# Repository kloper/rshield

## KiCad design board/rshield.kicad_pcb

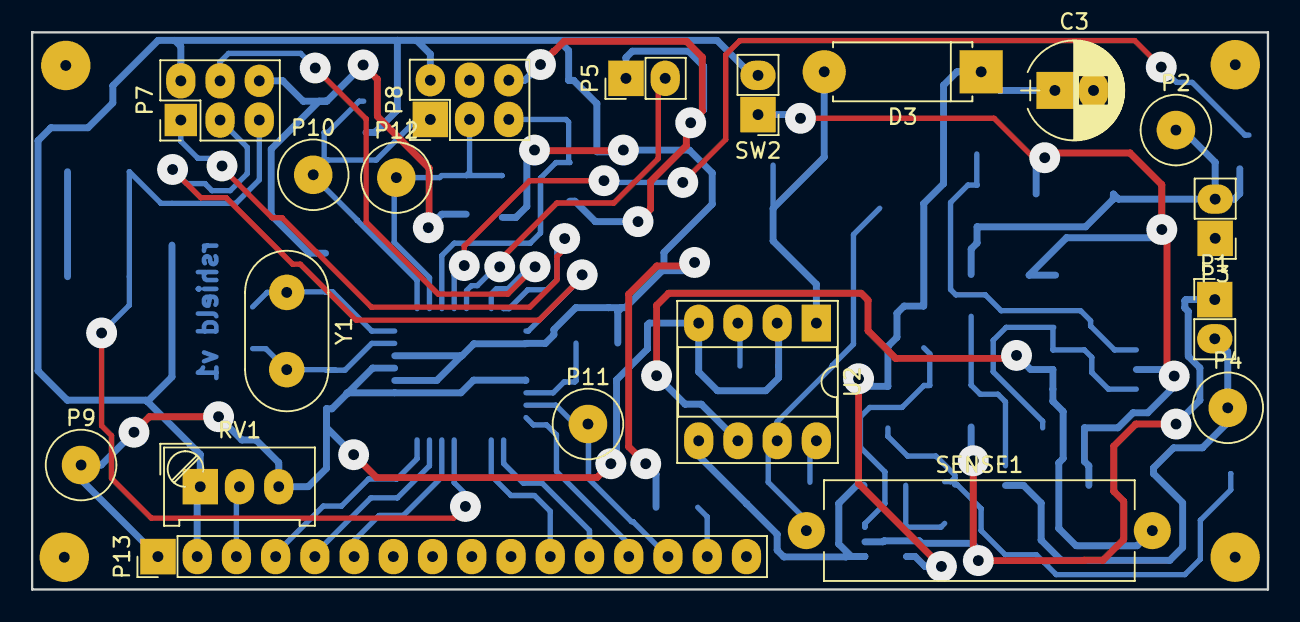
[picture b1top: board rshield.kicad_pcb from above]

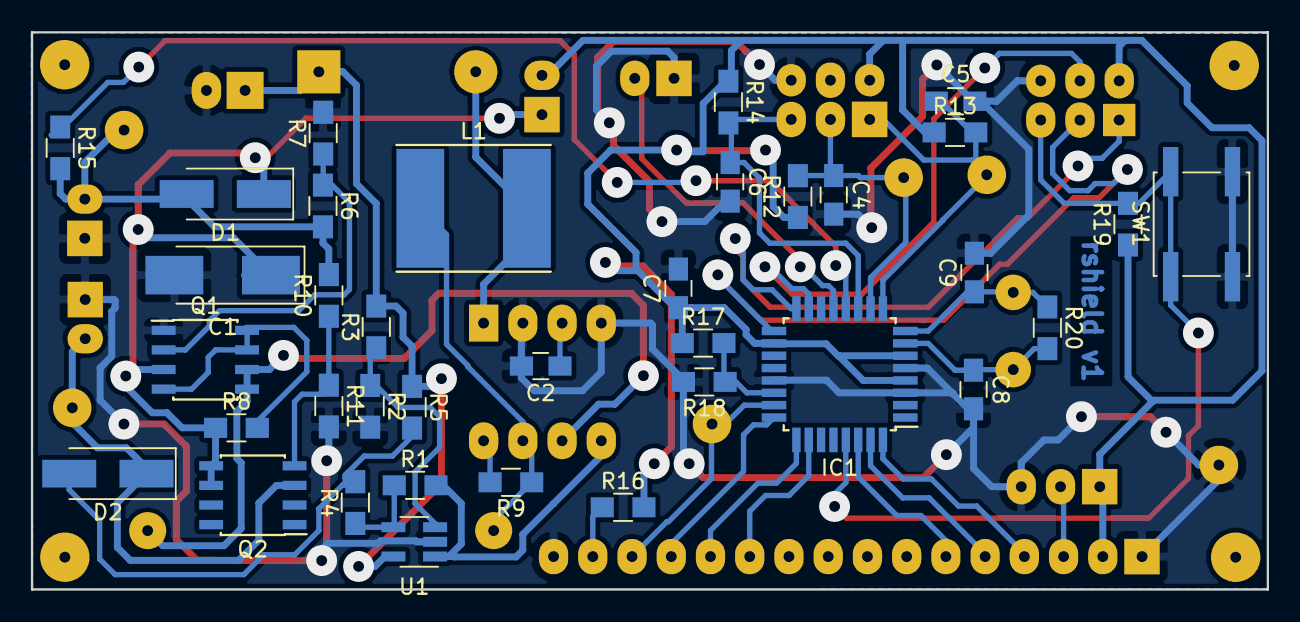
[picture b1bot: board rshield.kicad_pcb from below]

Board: 2 copper layers, 80.0 x 36.1 mm, 55 parts (36 on the bottom side), 39 nets.

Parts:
C1: 100uF; CP_Tantalum_Case-U_EIA-6032-15_Hand
C2: 700pF; C_0805_HandSoldering
C3: 220uF; CP_Radial_D6.3mm_P2.50mm
C4, C5, C6: 104pF; C_0805_HandSoldering
C7: 100nF; C_0805_HandSoldering
C8, C9: 22pF; C_0805_HandSoldering
D1, D2: RS1M; D_SMA_Handsoldering
D3: 1N5819; D_5W_P10.16mm_Horizontal
IC1: ATMEGA328P-A; TQFP-32_7x7mm_Pitch0.8mm
L1: 221uH; Inductor_Taiyo-Yuden_NR-80xx_HandSoldering
P1: CONN_BAT; Socket_Strip_Straight_1x02_Pitch2.54mm
P2: TP1_VCHARGE; 1pin
P3: CONN_VCHARGE; Pin_Header_Straight_1x02_Pitch2.54mm
P4: TP1_VBAT; 1pin
P5: CONN_GEIGER; Pin_Header_Straight_1x02_Pitch2.54mm
P7: CONN_SPI; Pin_Header_Straight_2x03_Pitch2.54mm
P8: CONN_ROT; Pin_Header_Straight_2x03_Pitch2.54mm
P9: TP_GND; 1pin
P10: TP_ROTA; 1pin
P11: TP_DB7; 1pin
P12: TP_ROTB; 1pin
P13: CONN_HD44780; Pin_Header_Straight_1x16_Pitch2.54mm
Q1, Q2: Si4562DY; SOIC-8_3.9x4.9mm_Pitch1.27mm
R1, R2, R3, R4, R8: 100K; R_0805_HandSoldering
R5: 22; R_0805_HandSoldering
R6, R10: 100; R_0805_HandSoldering
R7, R11, R18: 47K; R_0805_HandSoldering
R9: 180; R_0805_HandSoldering
R12, R13, R14: 3.6K; R_0805_HandSoldering
R15, R19: 10K; R_0805_HandSoldering
R16: 47; R_0805_HandSoldering
R17: 180K; R_0805_HandSoldering
R20: 1M; R_0805_HandSoldering
RV1: POT; Potentiometer_Trimmer_Bourns_PV36W
SENSE1: 0.5; R_Axial_Power_L20.0mm_W6.4mm_P22.40mm
SW1: SPST; SW_SPST_EVQQ2
SW2: SPST; Socket_Strip_Straight_1x02_Pitch2.54mm
U1: OPA237NA; SOT-23-5_HandSoldering
U2: MC34063A; DIP-8_W7.62mm_Socket_LongPads
Y1: 8MHz Crystal; Resonator-2pin_w10.0mm_h5.0mm

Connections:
/logic/+5V: C7.1, IC1.4, IC1.6, IC1.18, P7.2, P8.2, P13.2, R12.1, R13.1, R14.1, R16.2, R17.1, R19.1, RV1.1, SW2.2
/logic/DB4: IC1.26, P13.11
/logic/DB5: IC1.25, P13.12
/logic/DB6: IC1.24, P13.13
/logic/DB7: IC1.23, P11.1, P13.14
/logic/EN: IC1.30, P13.6
/logic/GCOUNT: IC1.13, P5.2
/logic/MISO: IC1.16, P7.1
/logic/MOSI: IC1.15, P7.4
/logic/ON_CHARGE: IC1.12, R15.1
/logic/ROTA: C5.1, IC1.9, P8.1, P10.1, R13.2
/logic/ROTB: C4.1, IC1.10, P8.3, P12.1, R12.2
/logic/ROTP: C6.1, IC1.11, P8.5, R14.2
/logic/RS: IC1.32, P13.4
/logic/RW: IC1.31, P13.5
/logic/SCK: IC1.17, P7.3
/logic/~RESET: IC1.29, P7.5, R19.2, SW1.1
/power/+5V: C1.1, D1.1, Q1.3, Q2.5, Q2.6, R8.1, SW2.1
/power/BOOST_CTRL: R1.2, U1.1, U2.5
/power/BOOST_IN: Q1.5, Q1.6, SENSE1.2, U2.6
/power/BOOST_OUT: C3.1, D3.1, R3.2, R5.1, U1.5
/power/VBAT: D2.1, P1.2, P4.1, Q2.3
/power/VCHARGE: D1.2, P2.1, P3.2, R6.2, R10.2, R15.2
Earth: C1.2, C2.2, C3.2, C4.2, C5.2, C6.2, C7.2, C8.2, C9.2, IC1.3, IC1.5, IC1.21, P1.1, P3.1, P5.1, P7.6, P8.6, P9.1, P13.1, P13.16, Q1.1, R2.2, R7.2, R11.2, R18.2, RV1.3, SW1.2, U1.2, U2.2, U2.4
unnamed: C2.1, U2.3
unnamed: C8.1, IC1.7, R20.2, Y1.2
unnamed: C9.1, IC1.8, R20.1, Y1.1
unnamed: D2.2, R4.2, R5.2
unnamed: D3.2, L1.2, U2.1
unnamed: IC1.22, R17.2, R18.1
unnamed: L1.1, R9.1, SENSE1.1, U2.7
unnamed: P13.3, RV1.2
unnamed: P13.15, R16.1
unnamed: Q1.2, R6.1, R7.1
unnamed: Q1.4, Q1.7, Q1.8, R8.2
unnamed: Q2.4, R10.1, R11.1
unnamed: R1.1, R4.1, U1.4
unnamed: R2.1, R3.1, U1.3
unnamed: R9.2, U2.8

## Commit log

2018-02-12 Initial working version of Radiation Shield board
2018-02-19 Put GCOUNT input on T1 ...
    ... Put ROTA in the former GCOUNT place instead.
    Note: the change is reflected in schematic only and
    needs to be reflected on layout later.
2018-02-19 Initail import of RadiationShield firmware ...
    ... Files timer, hd44780, timer and print were copied from
    uv-timer@github project verbatim, with very slight
    modifications.
2018-02-19 Initial import of the project box mechanics
